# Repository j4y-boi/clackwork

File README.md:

# clackwork
The alarm clock with a built in macropad mode! 

## About:
This project was built for [Hack Club Blare](https://blare.hackclub.com/index.html), I got the idea to add a macropad mode after seeing the microcontroller that we were supposed to use. It reminded me a lot of the RP2040-based microcontroller I used to build a macropad before and after some research I found out that the MCU we use supported Bluetooth. So, now you got an alarm clock that wakes you up, but you can also use it to game, which will probably keep you awake.
## Showcase:
The case and the PCB of the alarm clock:

GUI that the alarm clock will use (Designed in [Lopaka](https://lopaka.app/))

Schematic of the PCB:

3D model of the PCB itself:

PCB Wiring:

## BOM / Bill of Materials
| Item | Qty |
| :--- | :--- |
| Seeed XIAO ESP32C3 | 1x |
| MX-Style Keyboard Switches | 8x |
| White Blank DSA Keycaps | 8x |
| Through-Hole 1N4148 Diodes | 8x |
| 2.25in TFT Screen | 1x |
| 3.3V Piezo Buzzer | 1x |
| 2.54mm 8 Pin Male Header | 1x |
| 20cm Female-Female Jumper Wires | 8x |
| M3x5x4 Heatset Inserts | 8x |
| M3x8mm Screws | 4x |
| M3x16mm Screws | 4x |

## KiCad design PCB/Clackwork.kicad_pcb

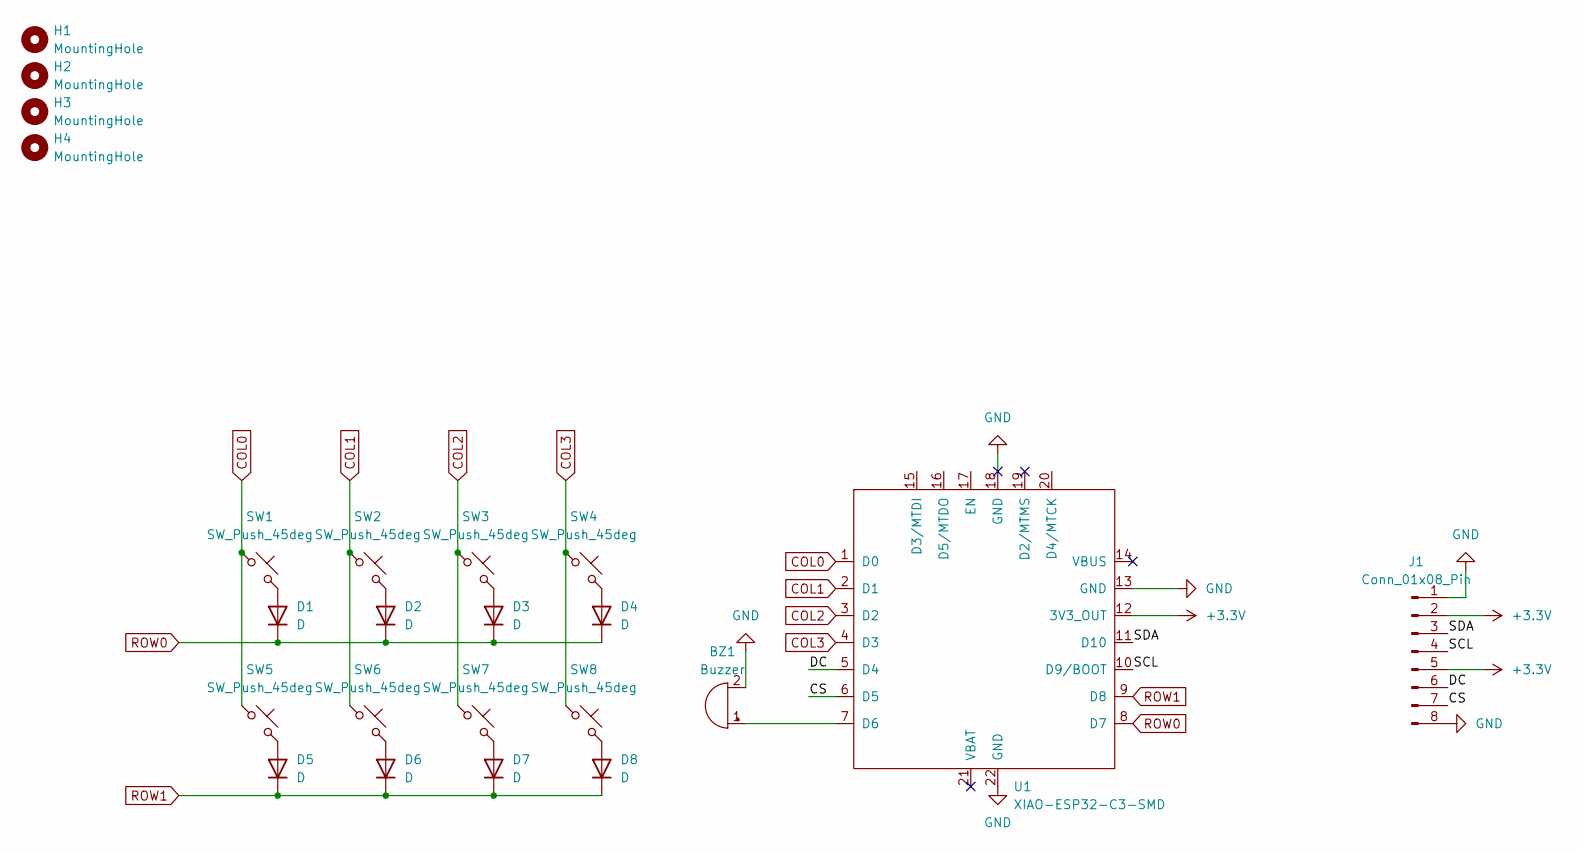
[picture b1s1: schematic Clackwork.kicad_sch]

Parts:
BZ1: Buzzer; Buzzer_12x9.5RM7.6
D1, D2, D3, D4, D5, D6, D7, D8: D; D_DO-35_SOD27_P7.62mm_Horizontal
H1, H2, H3, H4: MountingHole; MountingHole_3.2mm_M3
J1: Conn_01x08_Pin; PinSocket_1x08_P2.54mm_Vertical
SW1, SW2, SW3, SW4, SW5, SW6, SW7, SW8: SW_Push_45deg; SW_Cherry_MX_1.00u_PCB_3D
U1: XIAO-ESP32-C3-SMD; XIAO-ESP32-C3-DIP

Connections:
+3.3V: J1.2, J1.5, U1.12 (3V3_OUT)
/CS: J1.7, U1.6 (D5)
/DC: J1.6, U1.5 (D4)
/SCL: J1.4, U1.10 (D9/BOOT)
/SDA: J1.3, U1.11 (D10)
COL0: SW1.1, SW5.1, U1.1 (D0)
COL1: SW2.1, SW6.1, U1.2 (D1)
COL2: SW3.1, SW7.1, U1.3 (D2)
COL3: SW4.1, SW8.1, U1.4 (D3)
GND: BZ1.2 (-), J1.1, J1.8, U1.13 (GND), U1.18 (GND), U1.22 (GND)
unnamed: BZ1.1 (+), U1.7 (D6)
unnamed: D1.2 (A), SW1.2
unnamed: D2.2 (A), SW2.2
unnamed: D3.2 (A), SW3.2
unnamed: D4.2 (A), SW4.2
unnamed: D5.2 (A), SW5.2
unnamed: D6.2 (A), SW6.2
unnamed: D7.2 (A), SW7.2
unnamed: D8.2 (A), SW8.2
ROW0: D1.1 (K), D2.1 (K), D3.1 (K), D4.1 (K), U1.8 (D7)
ROW1: D5.1 (K), D6.1 (K), D7.1 (K), D8.1 (K), U1.9 (D8)

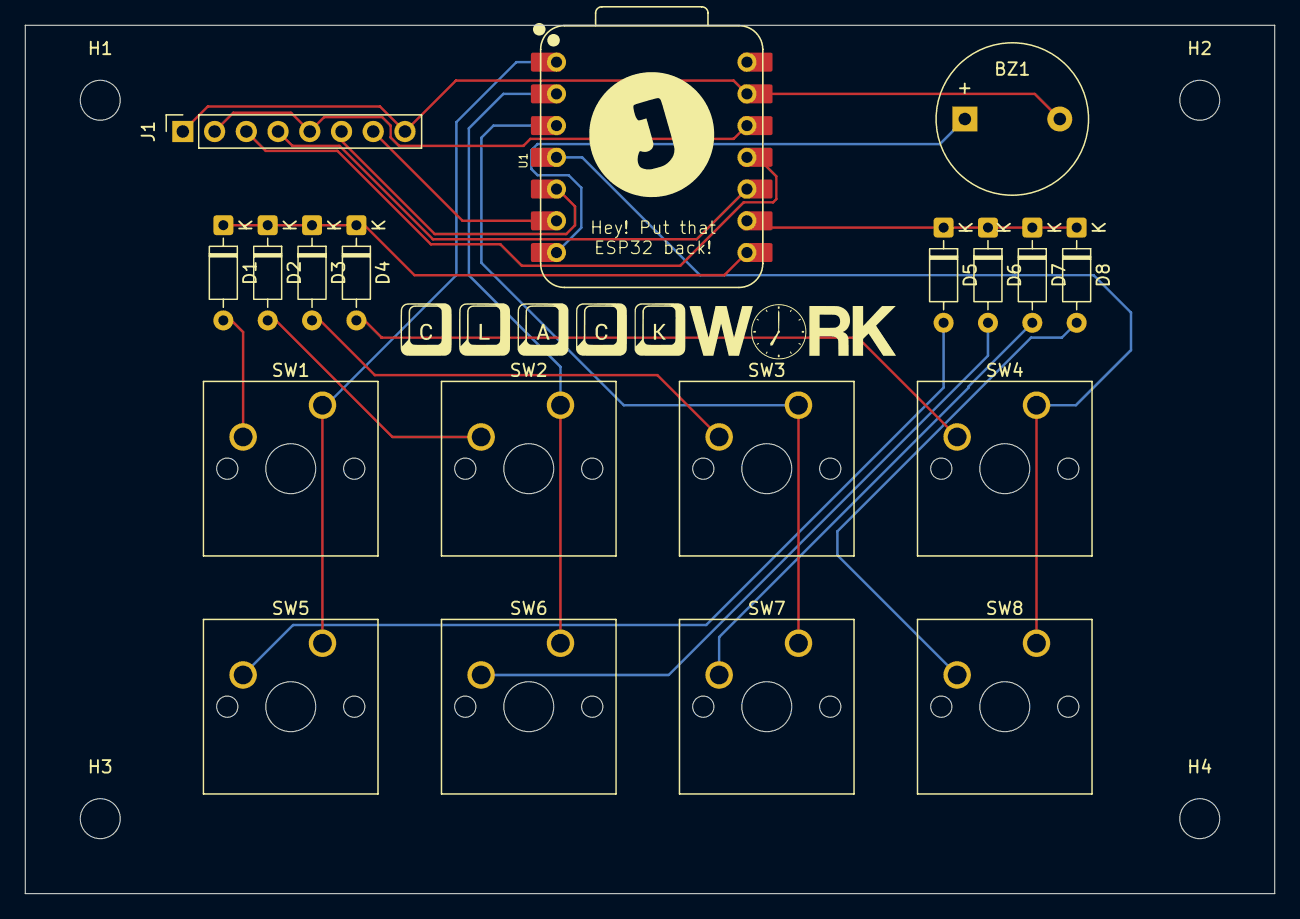
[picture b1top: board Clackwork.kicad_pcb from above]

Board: 2 copper layers, 100.0 x 69.5 mm, 23 parts (0 on the bottom side), 21 nets.
